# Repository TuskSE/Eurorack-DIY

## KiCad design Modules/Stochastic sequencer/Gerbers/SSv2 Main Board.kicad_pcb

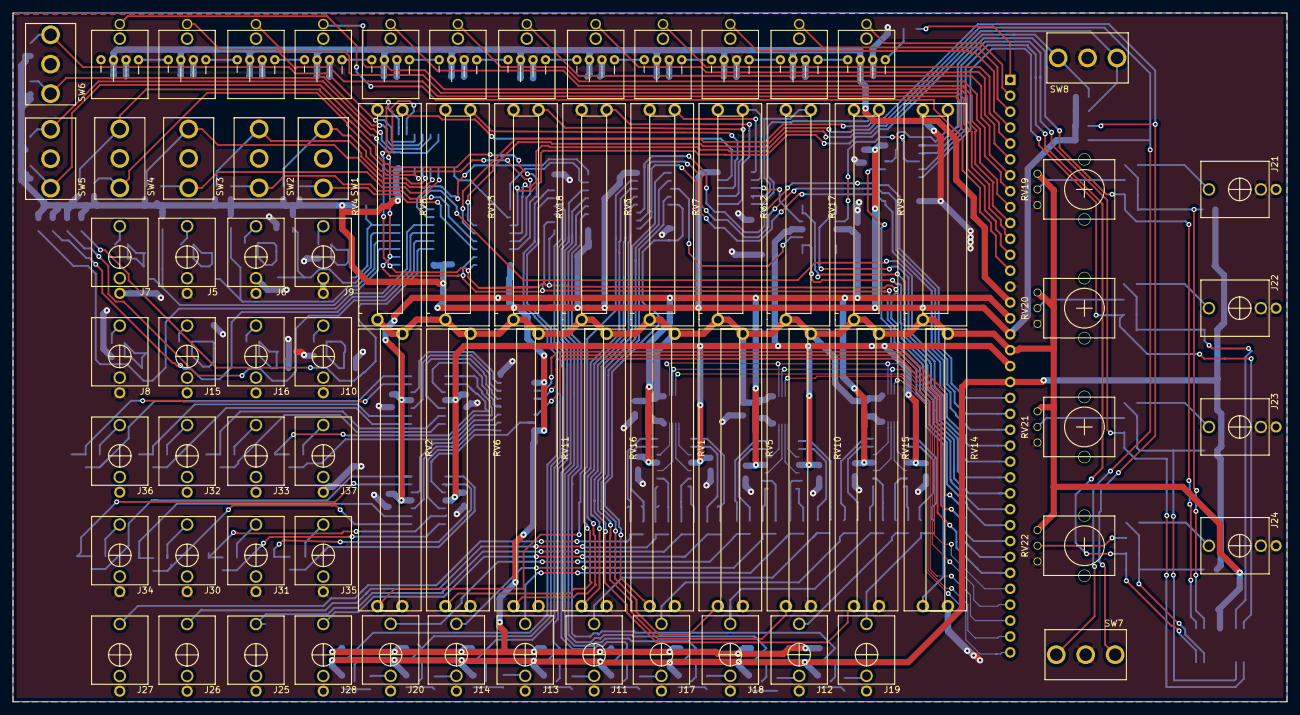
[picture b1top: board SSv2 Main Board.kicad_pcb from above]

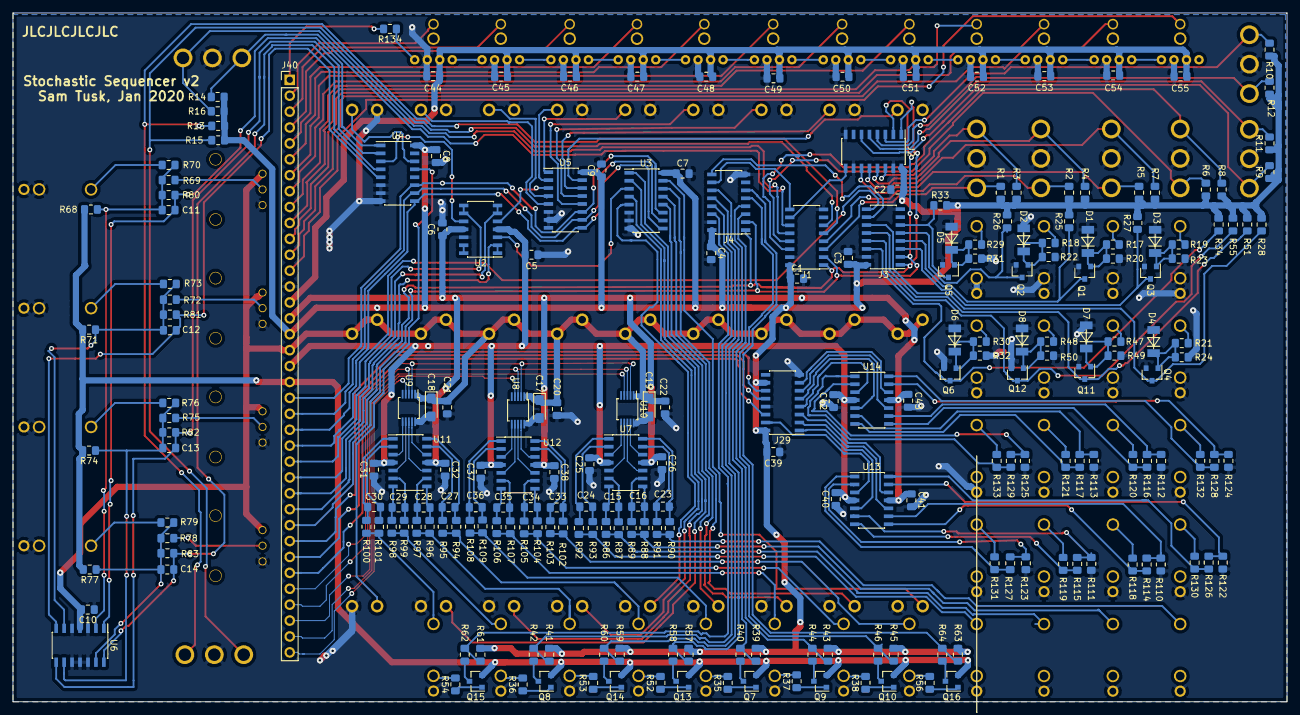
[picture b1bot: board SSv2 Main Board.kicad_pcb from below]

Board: 2 copper layers, 203.5 x 110.0 mm, 301 parts (227 on the bottom side), 242 nets.

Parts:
C1, C2, C3, C4, C5, C6, C7, C8, C9, C10, C25, C26, C31, C32, C37, C38, C39, C40, C41, C42, C43, C44, C45, C46, C47, C48, C49, C50, C51, C52, C53, C54, C55: 100nF; C_0805_2012Metric_Pad1.15x1.40mm_HandSolder
C11, C12, C13, C14: 1nF; C_0805_2012Metric_Pad1.15x1.40mm_HandSolder
C15, C16, C20, C21, C22, C23, C24, C27, C28, C29, C30, C33, C34, C35, C36: 100pF; C_0805_2012Metric_Pad1.15x1.40mm_HandSolder
C17, C18, C19: 10uF tantalum; CP_EIA-3216-18_Kemet-A_Pad1.58x1.35mm_HandSolder
D1, D2, D3, D4, D5, D6, D7, D8: FDLL4148; LL4148_sam
J1, J2, J3, J4: SN74HC165; SOIC-16_3.9x9.9mm_P1.27mm
J5, J6, J7, J8, J9, J10, J11, J12, J13, J14, J15, J16, J17, J18, J19, J20, J21, J22, J23, J24, J25, J26, J27, J28, J30, J31, J32, J33, J34, J35, J36, J37: PJ301M-12; PJ301M-12_Compact
J29: SN74HC595; SOIC-16_3.9x9.9mm_P1.27mm
J40: Conn_01x37_Male; PinHeader_1x37_P2.54mm_Vertical
Q1, Q2, Q3, Q4, Q5, Q6, Q7, Q8, Q9, Q10, Q11, Q12, Q13, Q14, Q15, Q16: BC847; SOT-23
R1, R2, R3, R4, R5, R6, R7, R8, R9, R10, R11, R12, R13, R14, R15, R16, R20, R22, R23, R24, R31, R32, R49, R50: 33k; R_0805_2012Metric_Pad1.15x1.40mm_HandSolder
R17, R18, R19, R21, R29, R30, R35, R36, R37, R38, R47, R48, R52, R53, R54, R56, R68, R70, R71, R73, R74, R76, R77, R79: 100k; R_0805_2012Metric_Pad1.15x1.40mm_HandSolder
R25, R26, R27, R28, R33, R34, R39, R41, R43, R45, R51, R55, R57, R59, R61, R63, R110, R111, R112, R113, R122, R123, R124, R125: 10k; R_0805_2012Metric_Pad1.15x1.40mm_HandSolder
R40, R42, R44, R46, R58, R60, R62, R64: 15k; R_0805_2012Metric_Pad1.15x1.40mm_HandSolder
R69, R72, R75, R78, R80, R81, R82, R83: 67k; R_0805_2012Metric_Pad1.15x1.40mm_HandSolder
R86, R88, R90, R92, R94, R96, R98, R100, R102, R104, R106, R108: 220R; R_0805_2012Metric_Pad1.15x1.40mm_HandSolder
R87, R89, R91, R93, R95, R97, R99, R101, R103, R105, R107, R109: 4.7k; R_0805_2012Metric_Pad1.15x1.40mm_HandSolder
R114, R115, R116, R117, R126, R127, R128, R129: 20k; R_0805_2012Metric_Pad1.15x1.40mm_HandSolder
R118, R119, R120, R121, R130, R131, R132, R133: 1k; R_0805_2012Metric_Pad1.15x1.40mm_HandSolder
R134: 200R; R_0805_2012Metric_Pad1.15x1.40mm_HandSolder
RV1, RV2, RV5, RV6, RV10, RV11, RV14, RV15, RV16: 100k lin; Tayda A-1629 Slide Pot_30mm
RV3, RV4, RV7, RV8, RV9, RV12, RV13, RV17, RV18: 100k lin; Tayda A-1623 Slide Pot_20mm
RV19, RV20, RV21, RV22: 10k; Alpha9mmPot
SW1, SW2, SW3, SW4, SW5, SW6, SW7, SW8: SW_SPDT; SPDT toggle on-off-on
U2, U7, U11, U12, U13, U14: TL074; SOIC-14_3.9x8.7mm_P1.27mm
U3, U4, U5: 74HC4051; SOIC-16_3.9x9.9mm_P1.27mm
U6: MCP6004; SOIC-14_3.9x8.7mm_P1.27mm
U8, U9, U10: MCP4728; MSOP-10_3x3mm_P0.5mm
U16, U18, U19, U20, U21, U22, U23, U24, U25, U26, U27, U28: LedTouchJack

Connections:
3.3V_Analogue: C10.2, C17.1, C18.1, C19.1, C20.1, C21.1, C22.1, J40.18, RV1.3, RV2.3, RV3.3, RV4.3, RV5.3, RV6.3, RV7.3, RV8.3, RV9.3, RV10.3, RV11.3, RV12.3, RV13.3, RV14.3, RV15.3, RV16.3, RV17.3, RV18.3, RV19.1, RV20.1, RV21.1, RV22.1, U6.4, U8.1, U9.1, U10.1
3.3V_Digital: C1.1, C2.1, C3.1, C4.1, C7.1, C8.1, C9.1, C39.1, J1.16, J2.16, J3.16, J4.16, J29.10, J29.16, J40.17, R1.1, R2.1, R3.1, R4.1, R5.1, R6.1, R7.1, R8.1, R9.1, R10.1, R11.1, R12.1, R13.1, R14.1, R15.1, R16.1, R25.2, R26.2, R27.2, R28.2, R33.2, R34.2, R39.1, R41.1, R43.1, R45.1, R51.2, R55.2, R57.1, R59.1, R61.1, R63.1, U3.16, U4.16, U5.16
+5V: C44.1, C45.1, C46.1, C47.1, C48.1, C49.1, C50.1, C51.1, C52.1, C53.1, C54.1, C55.1, J40.15, U16.5, U18.5, U19.5, U20.5, U21.5, U22.5, U23.5, U24.5, U25.5, U26.5, U27.5, U28.5
+12V: C5.2, C25.2, C31.2, C37.2, C40.2, C42.2, J40.19, U2.4, U7.4, U11.4, U12.4, U13.4, U14.4
-5V: J40.20, Q7.2, Q8.2, Q9.2, Q10.2, Q13.2, Q14.2, Q15.2, Q16.2, R68.2, R71.2, R74.2, R77.2
-12V: C6.2, C26.1, C32.1, C38.1, C41.1, C43.1, J40.16, U2.11, U7.11, U11.11, U12.11, U13.11, U14.11
/Analog Inputs/CVin1: J21.3, R70.2
/Analog Inputs/CVin2: J22.3, R73.2
/Analog Inputs/CVin3: J23.3, R76.2
/Analog Inputs/CVin4: J24.3, R79.2
/Analog Inputs/CVslider0: RV14.2, U4.13
/Analog Inputs/CVslider1: RV2.2, U3.15
/Analog Inputs/CVslider2: RV6.2, U3.14
/Analog Inputs/CVslider3: RV11.2, U3.13
/Analog Inputs/CVslider4: RV16.2, U3.12
/Analog Inputs/CVslider5: RV1.2, U3.5
/Analog Inputs/CVslider6: RV5.2, U3.4
/Analog Inputs/CVslider7: RV10.2, U3.2
/Analog Inputs/CVslider8: RV15.2, U3.1
/Analog Inputs/Control1: R69.2, RV19.2
/Analog Inputs/Control2: R72.2, RV20.2
/Analog Inputs/Control3: R75.2, RV21.2
/Analog Inputs/Control4: R78.2, RV22.2
/Analog Inputs/Pslider0: RV9.2, U4.14
/Analog Inputs/Pslider1: RV4.2, U5.15
/Analog Inputs/Pslider2: RV8.2, U5.14
/Analog Inputs/Pslider3: RV13.2, U5.13
/Analog Inputs/Pslider4: RV18.2, U5.12
/Analog Inputs/Pslider5: RV3.2, U5.1
/Analog Inputs/Pslider6: RV7.2, U5.2
/Analog Inputs/Pslider7: RV12.2, U5.4
/Analog Inputs/Pslider8: RV17.2, U5.5
/CV and Accent outputs/AccentOutA: U7.10, U10.8
/CV and Accent outputs/AccentOutALL: U7.12, U10.9
/CV and Accent outputs/AccentOutALL_Jack: J27.3, R90.1, R91.2
/CV and Accent outputs/AccentOutA_Jack: J26.3, R88.1, R89.2
/CV and Accent outputs/AccentOutB: U7.5, U10.7
/CV and Accent outputs/AccentOutB_Jack: J25.3, R86.1, R87.2
/CV and Accent outputs/AccentOutC: U7.3, U10.6
/CV and Accent outputs/AccentOutC_Jack: J28.3, R92.1, R93.2
/CV and Accent outputs/DAQ1: U8.9, U12.12
/CV and Accent outputs/DAQ2: U8.8, U12.10
/CV and Accent outputs/DAQ3: U8.7, U12.5
/CV and Accent outputs/DAQ4: U8.6, U12.3
/CV and Accent outputs/DAQ5: U9.9, U11.12
/CV and Accent outputs/DAQ6: U9.8, U11.10
/CV and Accent outputs/DAQ7: U9.7, U11.5
/CV and Accent outputs/DAQ8: U9.6, U11.3
/Digital Outputs/CycleOutA: J29.6, U14.10
/Digital Outputs/CycleOutAJack: J32.3, R120.2
/Digital Outputs/CycleOutALL: J29.7, U14.12
/Digital Outputs/CycleOutALLJack: J36.3, R132.2
/Digital Outputs/CycleOutB: J29.5, U14.5
/Digital Outputs/CycleOutBJack: J33.3, R121.2
/Digital Outputs/CycleOutC: J29.4, U14.3
/Digital Outputs/CycleOutCJack: J37.3, R133.2
/Digital Outputs/TrigOutA: J29.2, U13.10
/Digital Outputs/TrigOutAJack: J30.3, R118.2
/Digital Outputs/TrigOutALL: J29.3, U13.12
/Digital Outputs/TrigOutALLJack: J34.3, R130.2
/Digital Outputs/TrigOutB: J29.1, U13.5
/Digital Outputs/TrigOutBJack: J31.3, R119.2
/Digital Outputs/TrigOutC: J29.15, U13.3
/Digital Outputs/TrigOutCJack: J35.3, R131.2
/DigitalInputs and Normalization Probes/ClockInALL_Jack: J7.3, R19.2
/DigitalInputs and Normalization Probes/ClockInA_Jack: J5.3, R17.2
/DigitalInputs and Normalization Probes/ClockInB_Jack: J6.3, R18.2
/DigitalInputs and Normalization Probes/ClockInC_Jack: J9.3, R29.2
/DigitalInputs and Normalization Probes/CycleInALL_Jack: J8.3, R21.2
/DigitalInputs and Normalization Probes/CycleInA_Jack: J15.3, R47.2
/DigitalInputs and Normalization Probes/CycleInB_Jack: J16.3, R48.2
/DigitalInputs and Normalization Probes/CycleInC_Jack: J10.3, R30.2
/DigitalInputs and Normalization Probes/D16: J1.12, R16.2, SW8.3
/DigitalInputs and Normalization Probes/S1: J1.3, R1.2, SW1.1
/DigitalInputs and Normalization Probes/S2: J2.14, R3.2, SW1.3
/DigitalInputs and Normalization Probes/S3: J2.11, R5.2, SW3.1
/DigitalInputs and Normalization Probes/S4: J2.12, R7.2, SW3.3
/DigitalInputs and Normalization Probes/S5: J2.6, R9.2, SW5.1
/DigitalInputs and Normalization Probes/S6: J2.5, R11.2, SW5.3
/DigitalInputs and Normalization Probes/S7: J1.5, R13.2, SW7.1
/DigitalInputs and Normalization Probes/S8: J1.6, R15.2, SW7.3
/DigitalInputs and Normalization Probes/S9: J1.4, R2.2, SW2.1
/DigitalInputs and Normalization Probes/S10: J2.13, R4.2, SW2.3
/DigitalInputs and Normalization Probes/S11: J1.13, R6.2, SW4.1
/DigitalInputs and Normalization Probes/S12: J1.14, R8.2, SW4.3
/DigitalInputs and Normalization Probes/S13: J2.3, R10.2, SW6.3
/DigitalInputs and Normalization Probes/S14: J2.4, R12.2, SW6.1
/DigitalInputs and Normalization Probes/S15: J1.11, R14.2, SW8.1
AreadCon1: J40.27, U2.1, U2.2
AreadCon2: J40.26, U2.6, U2.7
AreadCon3: J40.25, U2.8, U2.9
AreadMuxControlPin1: J40.21, U3.11, U4.11, U5.11
AreadMuxControlPin2: J40.22, U3.10, U4.10, U5.10
AreadMuxControlPin3: J40.23, U3.9, U4.9, U5.9
CVin1buf: C11.2, R80.1, U4.1, U6.1
CVin2buf: C12.2, R81.1, U4.5, U6.7
CVin3buf: C13.2, R82.1, U4.2, U6.8
CVin4buf: C14.2, R83.1, U4.4, U6.14
ClockInA: J3.4, Q1.3, R25.1
ClockInALL: J3.3, Q3.3, R27.1
ClockInB: J3.5, Q2.3, R26.1
ClockInC: J3.6, Q5.3, R33.1
CycleInA: J3.12, Q11.3, R51.1
CycleInALL: J3.11, Q4.3, R28.1
CycleInB: J3.13, Q12.3, R55.1
CycleInC: J3.14, Q6.3, R34.1
DAC_A_LDACpin: J40.36, U8.4
DAC_B_LDACpin: J40.37, U9.4
DAC_C_LDACpin: J40.35, U10.4
DAC_SCLpin: J40.33, U8.2, U9.2, U10.2
DAC_SDApin: J40.34, U8.3, U9.3, U10.3
DAQout1: J20.3, R102.1, R103.2
DAQout2: J14.3, R104.1, R105.2
DAQout3: J13.3, R106.1, R107.2
DAQout4: J11.3, R108.1, R109.2
DAQout5: J17.3, R94.1, R95.2
DAQout6: J18.3, R96.1, R97.2
DAQout7: J12.3, R98.1, R99.2
DAQout8: J19.3, R100.1, R101.2
Din_CLKpin: J1.2, J2.2, J3.2, J4.2, J40.29
Din_SERpin: J3.9, J40.24
Din_latchPin: J1.1, J2.1, J3.1, J4.1, J40.28
Dout_CLKpin: J29.11, J40.30
Dout_LATCHpin: J29.12, J40.31
Dout_SERpin: J29.14, J40.32
GND: C1.2, C2.2, C3.2, C4.2, C5.1, C6.1, C7.2, C8.2, C9.2, C10.1, C17.2, C18.2, C19.2, C20.2, C21.2, C22.2, C25.1, C26.2, C31.1, C32.2, C37.1, C38.2, C39.2, C40.1, C41.2, C42.1, C43.2, C44.2, C45.2, C46.2, C47.2, C48.2, C49.2, C50.2, C51.2, C52.2, C53.2, C54.2, C55.2, D1.2, D2.2, D3.2, D4.2, D5.2, D6.2, D7.2, D8.2, J1.8, J1.15, J2.8, J2.10, J2.15, J3.8, J3.15, J4.8, J4.15, J5.1, J5.2, J6.1, J6.2, J7.1, J7.2, J8.1, J8.2, J9.1, J9.2, J10.1, J10.2, J11.1, J12.1, J13.1, J14.1, J15.1, J15.2, J16.1, J16.2, J17.1, J18.1, J19.1, J20.1, J21.1, J21.2, J22.1, J22.2, J23.1, J23.2, J24.1, J24.2, J25.1, J26.1, J27.1, J28.1, J29.8, J29.13, J30.1, J31.1, J32.1, J33.1, J34.1, J35.1, J36.1, J37.1, J40.14, Q1.2, Q2.2, Q3.2, Q4.2, Q5.2, Q6.2, Q11.2, Q12.2, R20.1, R22.1, R23.1, R24.1, R31.1, R32.1, R49.1, R50.1, R110.1, R111.1, R112.1, R113.1, R122.1, R123.1, R124.1, R125.1, RV1.1, RV2.1, RV3.1, RV4.1, RV5.1, RV6.1, RV7.1, RV8.1, RV9.1, RV10.1, RV11.1, RV12.1, RV13.1, RV14.1, RV15.1, RV16.1, RV17.1, RV18.1, RV19.3, RV20.3, RV21.3, RV22.3, SW1.2, SW2.2, SW3.2, SW4.2, SW5.2, SW6.2, SW7.2, SW8.2, U2.12, U3.6, U3.7, U3.8, U4.6, U4.7, U4.8, U5.6, U5.7, U5.8, U6.3, U6.5, U6.10, U6.11, U6.12, U8.10, U9.10, U10.10, U16.4, U18.4, U19.4, U20.4, U21.4, U22.4, U23.4, U24.4, U25.4, U26.4, U27.4, U28.4
unnamed: C11.1, R68.1, R69.1, R70.1, R80.2, U6.2
unnamed: C12.1, R71.1, R72.1, R73.1, R81.2, U6.6
unnamed: C13.1, R74.1, R75.1, R76.1, R82.2, U6.9
unnamed: C14.1, R77.1, R78.1, R79.1, R83.2, U6.13
unnamed: C15.1, R86.2, U7.7
unnamed: C15.2, R87.1, U7.6
unnamed: C16.1, R88.2, U7.8
unnamed: C16.2, R89.1, U7.9
unnamed: C23.1, R90.2, U7.14
unnamed: C23.2, R91.1, U7.13
unnamed: C24.1, R92.2, U7.1
unnamed: C24.2, R93.1, U7.2
unnamed: C27.1, R94.2, U11.14
unnamed: C27.2, R95.1, U11.13
unnamed: C28.1, R96.2, U11.8
unnamed: C28.2, R97.1, U11.9
unnamed: C29.1, R98.2, U11.7
unnamed: C29.2, R99.1, U11.6
unnamed: C30.1, R100.2, U11.1
unnamed: C30.2, R101.1, U11.2
unnamed: C33.1, R102.2, U12.14
unnamed: C33.2, R103.1, U12.13
unnamed: C34.1, R104.2, U12.8
unnamed: C34.2, R105.1, U12.9
unnamed: C35.1, R106.2, U12.7
unnamed: C35.2, R107.1, U12.6
unnamed: C36.1, R108.2, U12.1
unnamed: C36.2, R109.1, U12.2
unnamed: D1.1, Q1.1, R17.1, R20.2
unnamed: D2.1, Q2.1, R18.1, R22.2
unnamed: D3.1, Q3.1, R19.1, R23.2
unnamed: D4.1, Q4.1, R21.1, R24.2
unnamed: D5.1, Q5.1, R29.1, R31.2
unnamed: D6.1, Q6.1, R30.1, R32.2
unnamed: D7.1, Q11.1, R47.1, R49.2
unnamed: D8.1, Q12.1, R48.1, R50.2
unnamed: J1.9, J4.10
unnamed: J1.10, J2.9
unnamed: J3.10, J4.9
unnamed: J11.2, R35.2
unnamed: J12.2, R36.2
unnamed: J13.2, R37.2
unnamed: J14.2, R38.2
unnamed: J17.2, R52.2
unnamed: J18.2, R53.2
unnamed: J19.2, R54.2
unnamed: J20.2, R56.2
unnamed: Q7.1, R35.1
unnamed: Q7.3, R40.2
unnamed: Q8.1, R36.1
unnamed: Q8.3, R42.2
unnamed: Q9.1, R37.1
unnamed: Q9.3, R44.2
unnamed: Q10.1, R38.1
unnamed: Q10.3, R46.2
unnamed: Q13.1, R52.1
unnamed: Q13.3, R58.2
unnamed: Q14.1, R53.1
unnamed: Q14.3, R60.2
unnamed: Q15.1, R54.1
unnamed: Q15.3, R62.2
unnamed: Q16.1, R56.1
unnamed: Q16.3, R64.2
unnamed: R110.2, R114.1, U13.9
unnamed: R111.2, R115.1, U13.6
unnamed: R112.2, R116.1, U14.9
unnamed: R113.2, R117.1, U14.6
unnamed: R114.2, R118.1, U13.8
unnamed: R115.2, R119.1, U13.7
unnamed: R116.2, R120.1, U14.8
unnamed: R117.2, R121.1, U14.7
unnamed: R122.2, R126.1, U13.13
unnamed: R123.2, R127.1, U13.2
unnamed: R124.2, R128.1, U14.13
unnamed: R125.2, R129.1, U14.2
unnamed: R126.2, R130.1, U13.14
unnamed: R127.2, R131.1, U13.1
unnamed: R128.2, R132.1, U14.14
unnamed: R129.2, R133.1, U14.1
unnamed: R134.1, U28.3
unnamed: U2.3, U3.3
unnamed: U2.5, U5.3
unnamed: U2.10, U4.3
unnamed: U2.13, U2.14
unnamed: U16.3, U18.6
unnamed: U18.3, U19.6
unnamed: U19.3, U20.6
unnamed: U20.3, U21.6
unnamed: U21.3, U22.6
unnamed: U22.3, U23.6
unnamed: U23.3, U24.6
unnamed: U24.3, U25.6
unnamed: U25.3, U26.6
unnamed: U26.3, U27.6
unnamed: U27.3, U28.6
NormalizationProbe1: J4.6, R63.2, R64.1
NormalizationProbe2: J4.5, R45.2, R46.1
NormalizationProbe3: J4.3, R43.2, R44.1
NormalizationProbe4: J4.4, R39.2, R40.1
NormalizationProbe5: J4.11, R57.2, R58.1
NormalizationProbe6: J4.12, R59.2, R60.1
NormalizationProbe7: J4.13, R41.2, R42.1
NormalizationProbe8: J4.14, R61.2, R62.1
Touch0: J40.13, U16.1
Touch1: J40.12, U18.1
Touch2: J40.11, U19.1
Touch3: J40.10, U20.1
Touch4: J40.9, U21.1
Touch5: J40.8, U22.1
Touch6: J40.7, U23.1
Touch7: J40.6, U24.1
Touch8: J40.5, U25.1
Touch9: J40.4, U26.1
Touch10: J40.3, U27.1
Touch11: J40.2, U28.1
WS2812_serial: J40.1, R134.2

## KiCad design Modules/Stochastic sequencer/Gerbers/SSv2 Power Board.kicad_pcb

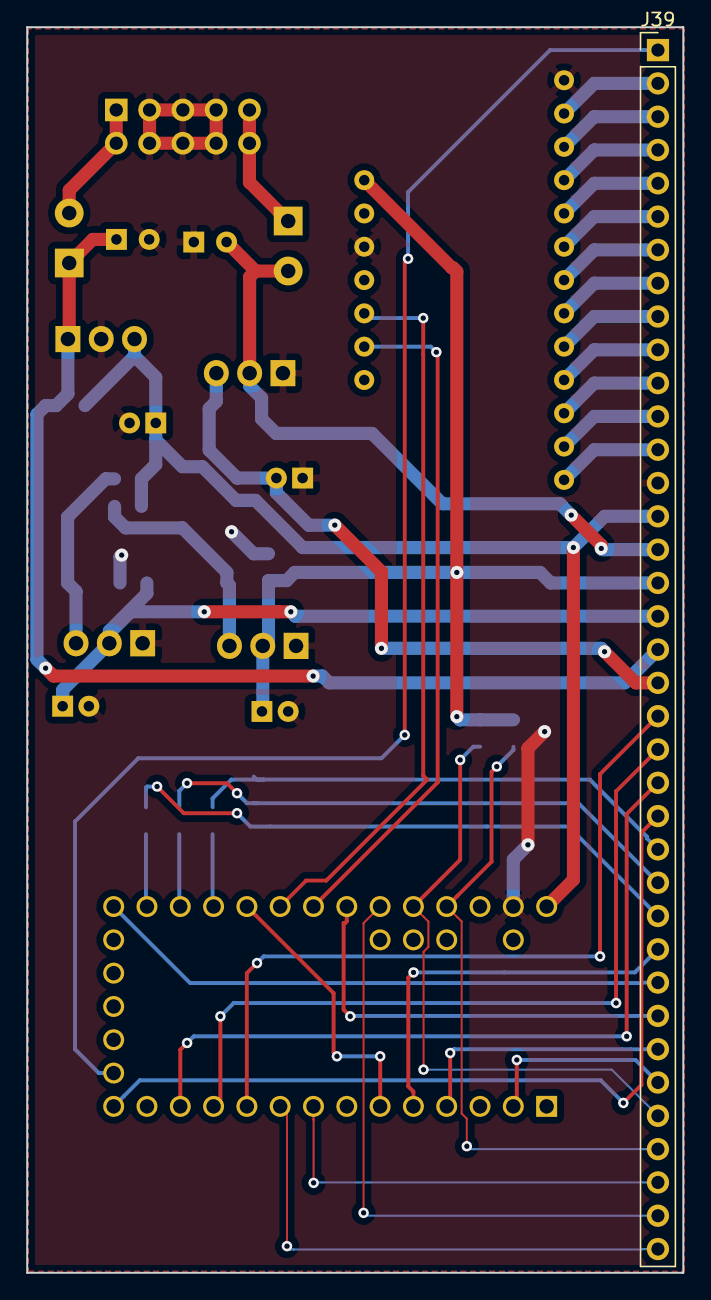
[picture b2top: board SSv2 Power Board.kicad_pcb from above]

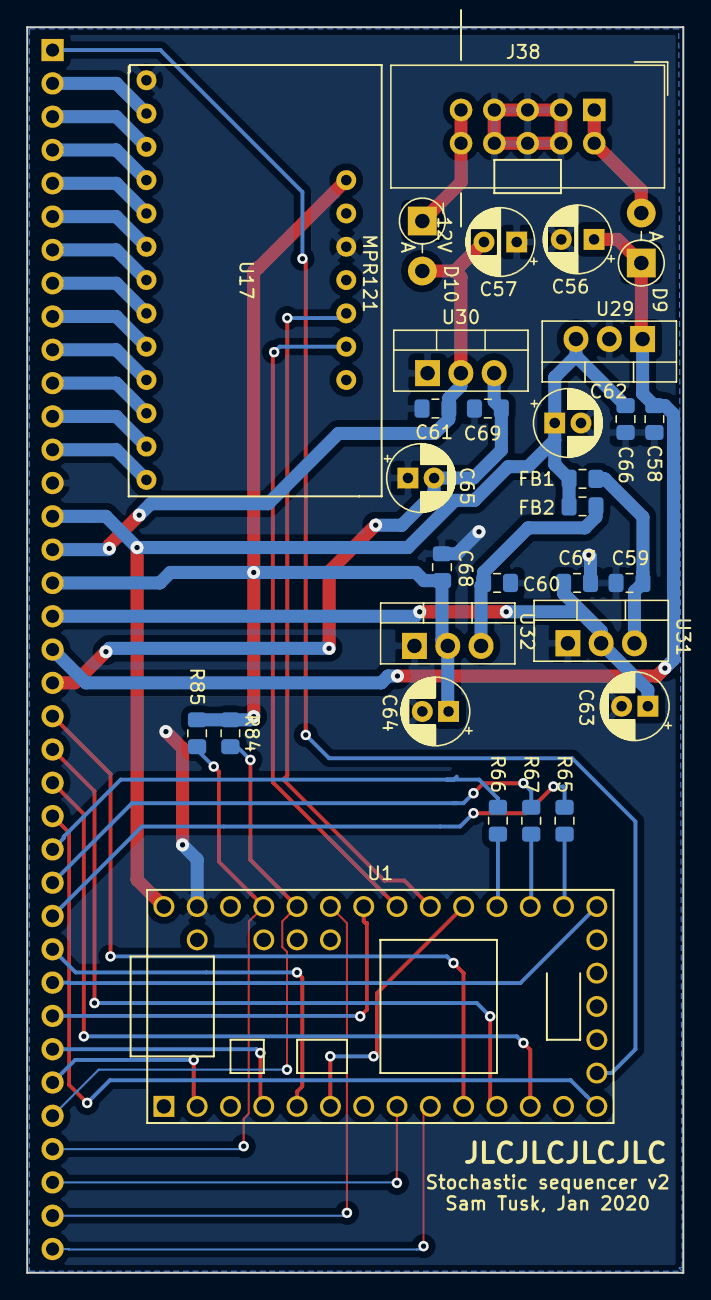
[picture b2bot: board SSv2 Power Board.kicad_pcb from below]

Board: 2 copper layers, 50.0 x 95.0 mm, 31 parts (30 on the bottom side), 47 nets.

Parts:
C56, C57: 100uF; CP_Radial_D5.0mm_P2.50mm
C58, C59, C60, C61, C66, C67, C68, C69: 100nF; C_0805_2012Metric_Pad1.15x1.40mm_HandSolder
C62, C63, C64, C65: 22uF; CP_Radial_D5.0mm_P2.00mm
D9, D10: 1N4001; D_DO-41_SOD81_P3.81mm_Vertical_AnodeUp
FB1, FB2: Ferrite_Bead; L_0805_2012Metric_Pad1.15x1.40mm_HandSolder
J38: EURO_PWR_2x5; Eurorack_power_header
J39: Conn_01x37_Female; PinHeader_1x37_P2.54mm_Vertical
R65, R66, R67: 2.2k; R_0805_2012Metric_Pad1.15x1.40mm_HandSolder
R84, R85: 4.7k; R_0805_2012Metric_Pad1.15x1.40mm_HandSolder
U1: Teensy-LC; TeensyLC_fixed_pads
U17: MPR121_breakout; MPR121 breakout (adafruit)
U29: LM7805_TO220; TO-220-3_Vertical
U30: LM7905_TO220; TO-220-3_Vertical
U31, U32: LM1117-3.3; TO-220-3_Vertical

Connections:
3.3V_Analogue: C63.1, C67.1, J39.18, U31.2
3.3V_Digital: C64.1, C68.1, J39.17, R84.1, R85.1, U17.19, U32.2
+5V: C62.1, C66.1, FB1.2, FB2.2, J39.15, U1.33, U29.3
+12V: C56.1, C58.1, D9.1, J39.19, U29.1
-5V: C65.2, C69.2, J39.20, U30.3
-12V: C57.2, C61.2, D10.2, J39.16, U30.2
/Power/+12V_in: D9.2, J38.1, J38.2
/Power/-12V_in: D10.1, J38.9, J38.10
/WS2812_level_boost: U1.6, U1.24
AreadCon1_p: J39.27, R65.1
AreadCon2_p: J39.26, R67.1
AreadCon3_p: J39.25, R66.1
AreadMuxControlPin1_p: J39.21, U1.10
AreadMuxControlPin2_p: J39.22, U1.11
AreadMuxControlPin3_p: J39.23, U1.12
AreadPin1_p: R65.2, U1.21
AreadPin2_p: R67.2, U1.22
AreadPin3_p: R66.2, U1.23
DAC_A_LDACpin_p: J39.36, U1.28
DAC_B_LDACpin_p: J39.37, U1.9
DAC_C_LDACpin_p: J39.35, U1.8
DAC_SCLpin_p: J39.33, R84.2, U1.29
DAC_SDApin_p: J39.34, R85.2, U1.30
Din_CLKpin_p: J39.29, U1.20
Din_SERpin_p: J39.24, U1.14
Din_latchPin_p: J39.28, U1.5
Dout_CLKpin_p: J39.30, U1.27
Dout_LATCHpin_p: J39.31, U1.4
Dout_SERpin_p: J39.32, U1.2
GND: C56.2, C57.1, C58.2, C59.2, C60.2, C61.1, C62.2, C63.2, C64.2, C65.1, C66.2, C67.2, C68.2, C69.1, J38.3, J38.4, J38.5, J38.6, J38.7, J38.8, J39.14, U1.32, U17.0, U17.17, U29.2, U30.1, U31.1, U32.1
unnamed: C59.1, FB1.1, U31.3
unnamed: C60.1, FB2.1, U32.3
Touch0_p: J39.13, U17.12
Touch1_p: J39.12, U17.11
Touch2_p: J39.11, U17.10
Touch3_p: J39.10, U17.9
Touch4_p: J39.9, U17.8
Touch5_p: J39.8, U17.7
Touch6_p: J39.7, U17.6
Touch7_p: J39.6, U17.5
Touch8_p: J39.5, U17.4
Touch9_p: J39.4, U17.3
Touch10_p: J39.3, U17.2
Touch11_p: J39.2, U17.1
TouchI2C_SCL_p: U1.26, U17.14
TouchI2C_SDA_p: U1.25, U17.15
WS2812_serial_p: J39.1, U1.15

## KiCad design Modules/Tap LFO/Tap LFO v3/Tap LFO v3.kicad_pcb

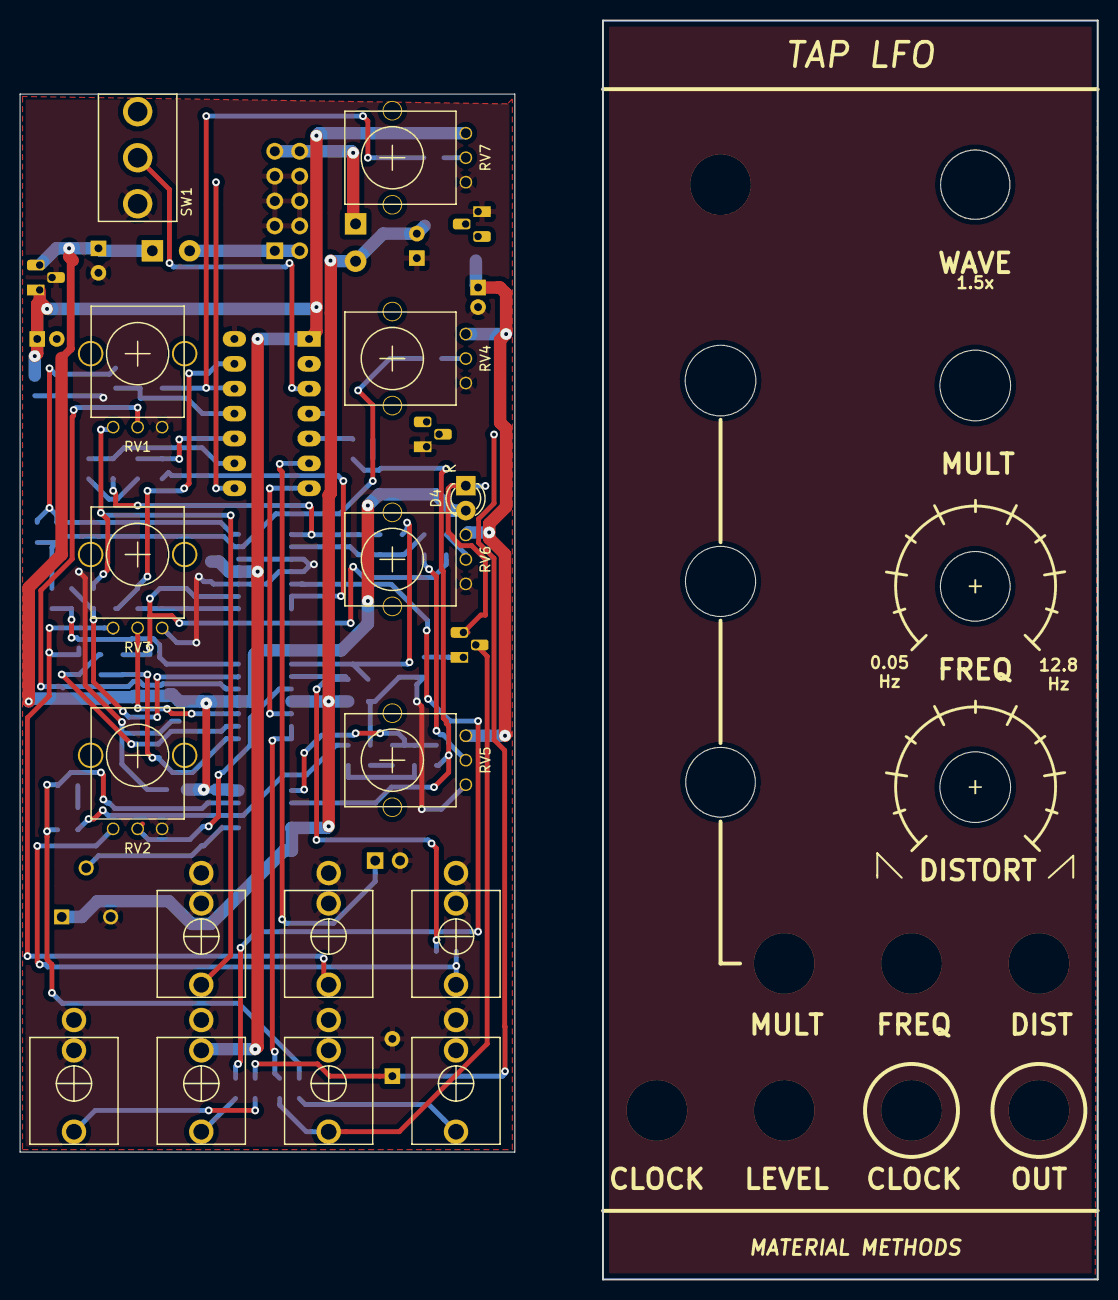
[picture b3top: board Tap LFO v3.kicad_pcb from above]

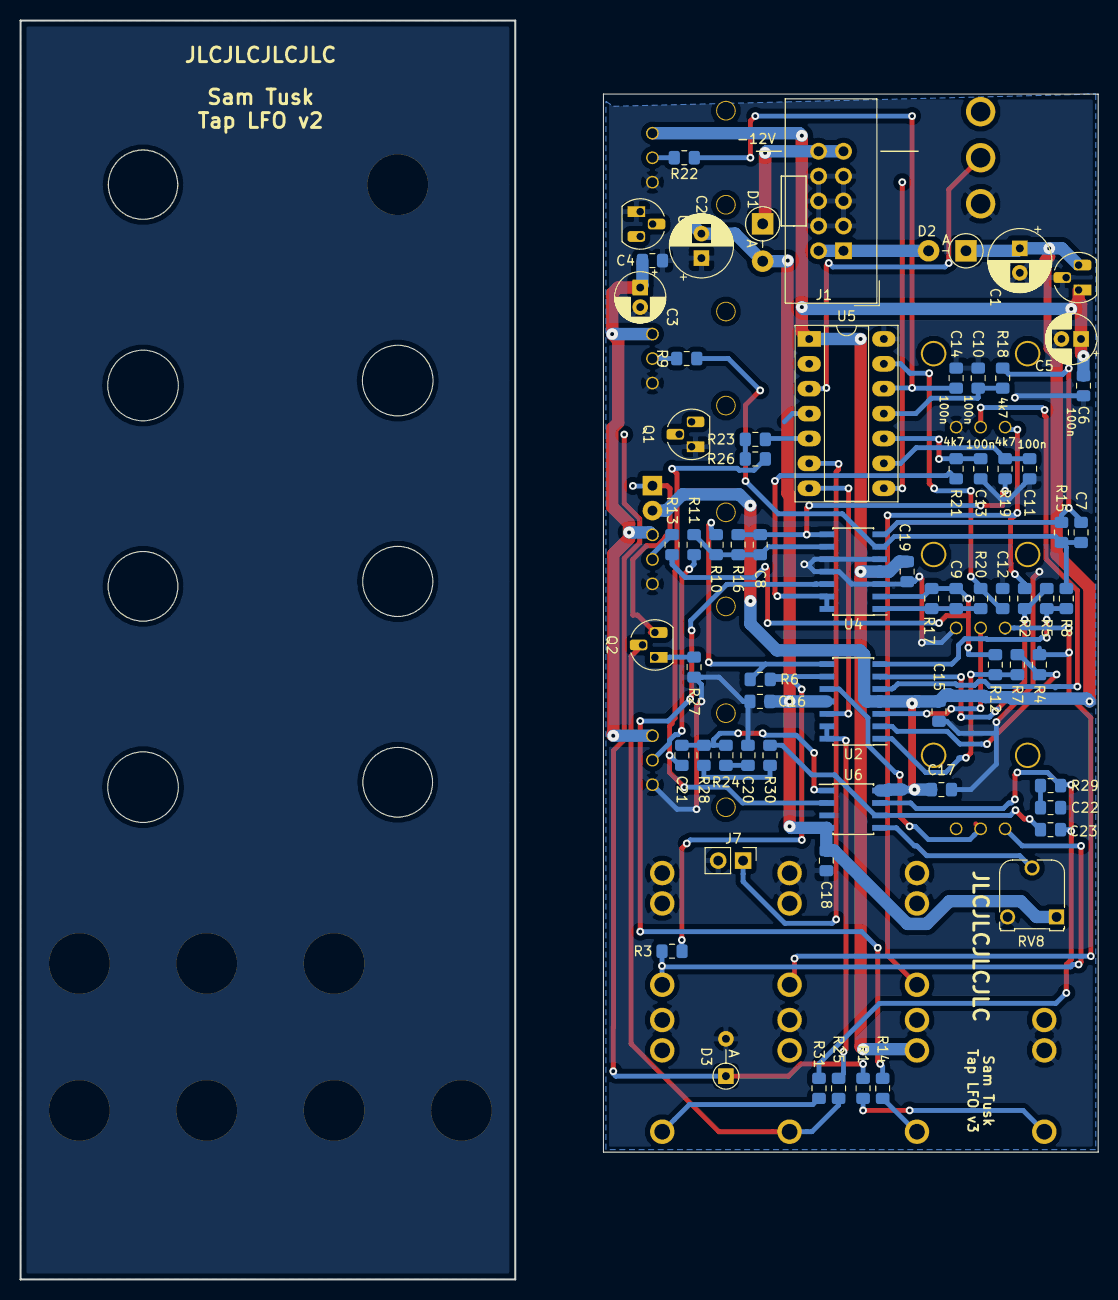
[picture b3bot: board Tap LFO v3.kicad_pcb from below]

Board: 2 copper layers, 50.5 x 108.0 mm, 84 parts (68 on the bottom side), 56 nets.

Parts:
C1, C2: 100uF; CP_Radial_D6.3mm_P2.50mm
C3, C5: 10uF; CP_Radial_D5.0mm_P2.00mm
C4, C6, C10, C11, C12, C13, C14, C15, C16, C17, C18, C19: 100nF; C_0805_2012Metric_Pad1.15x1.40mm_HandSolder
C7, C8, C9: 1nF; C_0805_2012Metric_Pad1.15x1.40mm_HandSolder
C20, C22: 10nF; C_0805_2012Metric_Pad1.15x1.40mm_HandSolder
C21, C23: 2.2nF; C_0805_2012Metric_Pad1.15x1.40mm_HandSolder
D1, D2: 1N4001; D_DO-41_SOD81_P3.81mm_Vertical_AnodeUp
D3: 1N4148; D_DO-35_SOD27_P3.81mm_Vertical_AnodeUp
D4: LED; LED3mm
J1: EURO_PWR_2x5; Eurorack_power_header
J2, J3, J4, J5, J6, J8, J9: PJ301M-12; PJ301M-12-MoreMetal
J7: Conn_01x02_Male; PinHeader_1x02_P2.54mm_Vertical
Q1, Q2: 2N3904; TO-92_HandSolder
R1, R27, R28: 10k; R_0805_2012Metric_Pad1.15x1.40mm_HandSolder
R2, R3, R4, R5, R6, R7, R14: 200k; R_0805_2012Metric_Pad1.15x1.40mm_HandSolder
R8, R9, R10, R11, R12, R13, R16, R17: 100k; R_0805_2012Metric_Pad1.15x1.40mm_HandSolder
R15: 70k; R_0805_2012Metric_Pad1.15x1.40mm_HandSolder
R18, R19, R20, R21: 4k7; R_0805_2012Metric_Pad1.15x1.40mm_HandSolder
R22, R25, R31: 1k; R_0805_2012Metric_Pad1.15x1.40mm_HandSolder
R23, R24: 12k; R_0805_2012Metric_Pad1.15x1.40mm_HandSolder
R26: 47k; R_0805_2012Metric_Pad1.15x1.40mm_HandSolder
R29: 20k; R_0805_2012Metric_Pad1.15x1.40mm_HandSolder
R30: 24k; R_0805_2012Metric_Pad1.15x1.40mm_HandSolder
RV1, RV2, RV3: 100k lin; SongHuei9mmPot
RV4, RV5, RV6: 100k lin; Alpha9mmPot
RV7: 10k lin; Alpha9mmPot
RV8: 100k; Potentiometer_Runtron_RM-065_Vertical
SW1: SW_SPDT; SPDT toggle on-off-on
U1: L79L05_TO92; TO-92_HandSolder
U2: TL074; SOIC-14_3.9x8.7mm_P1.27mm
U3: LM78L05_TO92; TO-92_HandSolder
U4: MCP6004; SOIC-14_3.9x8.7mm_P1.27mm
U5: TAPLFO3; DIP-14_W7.62mm_Socket_LongPads
U6: TL072; SOIC-8_3.9x4.9mm_P1.27mm

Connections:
+5V: C5.1, C6.1, C19.1, J6.2, RV7.3, U3.1, U4.4, U5.1
+12V: C1.1, C15.1, C17.1, D2.1, D4.2, U2.4, U3.3, U6.8
-5V: C3.1, C4.1, RV4.3, RV5.3, RV6.3, U1.3
-12V: C2.2, C16.2, C18.2, D1.2, RV8.1, U1.2, U2.11, U6.4
/+12V_in: D2.2, J1.1, J1.2
/-12V_in: D1.1, J1.9, J1.10
/ClockOutJack: J8.3, Q2.2, R25.1
/ClockOutPin: U2.12, U5.7
/DistAttn: RV2.2, U2.10
/DistInJack: J4.3, R3.2, RV2.1
/DistKnob: R11.2, RV5.2
/DistPin: C11.1, R19.1, U5.9
/LFOoutJack: J9.3, R31.1
/LevelPin: C13.1, R21.1, U5.10
/Level_inJack: J6.3, R14.2
/MultInJack: J3.3, R2.2, RV1.1
/MultKnob: R9.2, RV4.2
/MultPin: C10.1, R18.1, U5.11
/MultiAttn: RV1.2, U2.5
/OutPin: R23.2, U5.5
/SmoothPin: J7.1, U5.6
/TapInJack: J2.3, R1.2
/TempoAttn: RV3.2, U2.3
/TempoInJack: J5.3, R4.2, RV3.1
/TempoKnob: R13.2, RV6.2
/TimePin: C12.1, R20.1, U5.13
/WaveKnob: R22.2, RV7.2
/WavePin: C14.1, R22.1, U5.12
/WavesetPin: SW1.2, U5.3
/tapPin: Q1.3, U5.4
GND: C1.2, C2.1, C3.2, C4.2, C5.2, C6.2, C10.2, C11.2, C12.2, C13.2, C14.2, C15.2, C16.1, C17.2, C18.1, C19.2, C20.2, C22.2, D3.2, J1.3, J1.4, J1.5, J1.6, J1.7, J1.8, J2.1, J2.2, J3.1, J3.2, J4.1, J4.2, J5.1, J5.2, J6.1, J7.2, J8.1, J9.1, Q1.1, R27.1, RV1.3, RV2.3, RV3.3, RV4.1, RV5.1, RV6.1, RV7.1, RV8.3, SW1.1, U1.1, U3.2, U4.3, U4.5, U4.10, U4.11, U5.14, U6.3
unnamed: C7.1, R15.2, R18.2, U4.7
unnamed: C7.2, R8.1, R9.1, R15.1, U4.6
unnamed: C8.1, R16.2, R19.2, U4.8
unnamed: C8.2, R10.1, R11.1, R16.1, U4.9
unnamed: C9.1, R17.2, R20.2, U4.1
unnamed: C9.2, R12.1, R13.1, R17.1, U4.2
unnamed: C20.1, R23.1, R24.1, R26.2
unnamed: C21.1, R24.2, R28.2, U6.1
unnamed: C21.2, R26.1, U6.2
unnamed: C22.1, R28.1, R29.1, R30.2
unnamed: C23.1, R29.2, R31.2, U6.7
unnamed: C23.2, R30.1, U6.6
unnamed: D3.1, Q1.2, R1.1
unnamed: D4.1, Q2.3
unnamed: Q2.1, R27.2
unnamed: R2.1, R5.2, U2.6
unnamed: R3.1, R6.2, U2.9
unnamed: R4.1, R7.2, U2.2
unnamed: R5.1, R8.2, U2.7
unnamed: R6.1, R10.2, U2.8
unnamed: R7.1, R12.2, U2.1
unnamed: R14.1, U4.12
unnamed: R21.2, U4.13, U4.14
unnamed: R25.2, U2.13, U2.14
unnamed: RV8.2, U6.5
